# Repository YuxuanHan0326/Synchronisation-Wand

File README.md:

# Synchronisation-Wand
- [Introduction](https://github.com/YuxuanHan0326/Synchronisation-Wand?tab=readme-ov-file#introduction)
- [Related Publications](https://github.com/YuxuanHan0326/Synchronisation-Wand?tab=readme-ov-file#related-publications)
- [Project Files and Documentation](https://github.com/YuxuanHan0326/Synchronisation-Wand?tab=readme-ov-file#project-files-and-documentation)
- [3D Design Overview](https://github.com/YuxuanHan0326/Synchronisation-Wand?tab=readme-ov-file#3d-design-overview)
- [Screen Overview](https://github.com/YuxuanHan0326/Synchronisation-Wand?tab=readme-ov-file#screen-overview)
- [PCB Design](https://github.com/YuxuanHan0326/Synchronisation-Wand?tab=readme-ov-file#pcb-design)
- [Basic Controls](https://github.com/YuxuanHan0326/Synchronisation-Wand?tab=readme-ov-file#basic-controls)
- [Flash the Firmware](https://github.com/YuxuanHan0326/Synchronisation-Wand?tab=readme-ov-file#flash-the-firmware)
- [Configure Parameters of the Firmware](https://github.com/YuxuanHan0326/Synchronisation-Wand?tab=readme-ov-file#configure-parameters-of-the-firmware)

## Project Files and Documentation
This repository contains the Synchronisation Wand hardware and firmware, plus the verification platform for the encoded EMP synchronisation method. For fast access:
- [Synchronisation Wand Firmware](https://github.com/YuxuanHan0326/Synchronisation-Wand/tree/main/Firmware)
- [Synchronisation Wand PCB](https://github.com/YuxuanHan0326/Synchronisation-Wand/tree/main/PCB%20V1)
- [Data Processing Script for Verification Platform](https://github.com/YuxuanHan0326/Synchronisation-Wand/tree/main/Verification/DataProcessing/scripts)
- [Collected Source Data](https://github.com/YuxuanHan0326/Synchronisation-Wand/tree/main/Verification/DataProcessing/data)
- [Verilog Implementation Files for Testbed](https://github.com/YuxuanHan0326/Synchronisation-Wand/tree/main/Verification/Testbed/new_single_synchronisation.srcs/sources_1/new)
- [Final Report](./Resources/docs/Final_Report.pdf)
- [Presentation Poster](./Resources/docs/Presentation_Poster.pdf)

The related publication focuses mainly on the Synchronisation Wand device and hardware design. The final report is complementary and covers the verification platform, encoded EMP synchronisation verification, data processing workflow, and analysis in more detail. The presentation poster is a concise visual summary of the verification work.

## Introduction
The *Synchronisation Wand* is an open-source hardware solution for synchronising multiple wireless inertial measurement unit sensors (IMU) using their onboard magnetometers. The device combines an ESP32-S3 micro-controller unit with an electromagnetic generator to create an encoded electromagnetic event which can be used to synchronise multiple IMU devices. The device also includes an onboard IMU, allowing the user to track the motion of the wand as well as perform a kinetic synchronising event.

The device includes an OLED display and 4 configuable push buttons for user interface to enhance the usability of the system. The device uses SD card as storage medium to store the synchronising data and onboard IMU data. WiFi is used to synchronise the RTC using SNTP from configurable NTP servers, e.g. *pool.ntp.org*.

## Related Publications
For further detail of this project:

- [The Wand Chooses the IMU - Open Source Hardware for Synchronising Wearables using Magnetometer](https://dl.acm.org/doi/10.1145/3675094.3678485)

For how the electromagnetic synchronising method works:

- [A magnetometer-based method for in-situ syncing of wearable inertial measurement units](https://doi.org/10.3389/fcomp.2024.1385392)

## 3D Design Overview

## Screen Overview

## PCB Design
The PCB of the synchronisation wand is designed using the open sourced PCB design software *KiCad*. The PCB files are completely open-sourced.

### Schematic

### Layout

### Stack-up Information
This device uses a 4 layer pcb, with a stack up of Signal-GND-GND-Signal.
The physical stack up of the pcb board is shown below:

## Basic Controls
- Press "MENU" button to switch between menus.
- Press "S-MENU" button to switch submenus.
- Press "ACT" button to activate / deactive functions.
- Long press for more than 4 seconds and release to put the device into deep sleep mode. Re-click the button to wake the device up.

**Note:**
Before performing IMU synchronisation or turning on onboard IMU, please make sure that WiFi is connected, time has been synchronised and SD card is plugged in and recognised.

To avoid data loss, the user should terminate the synchronisation group, turn off onboard IMU manually and use the *Eject* function under the *SD Card* menu before unplugging the SD card.

## Flash the Firmware
### Requirements
To change and rebuild the firmware, the Espressif's IoT Development Framework (ESP-IDF) is needed. Installation instructions for the latest version of the ESP-IDF can be found in [this documentation](https://docs.espressif.com/projects/esp-idf/en/latest/esp32/get-started/). The firmware is tested on ESP-IDF version 5.2.1.

### ESP32S3 External Oscillator issue in ESP-IDF 5.2.1
ESP-IDF 5.2.1 has an ESP32-S3 RTC 32 kHz external oscillator setup issue: the clock tree code applies the internal 32 kHz crystal driver settings to the external oscillator path. On this hardware, the default values do not reliably drive the RTC slow clock.

If you build with ESP-IDF 5.2.1, manually override the XTAL32K configuration in the ESP-IDF clock tree source with these recommended starting values:

```c
.dac  = 0,
.dres = 0,
.dgm  = 0,
.dbuf = 1,
```

Alternatively, try a newer ESP-IDF release, where the ESP32-S3 external oscillator path may already be fixed. To confirm whether the oscillator started correctly, check the warning log printed during device power-up. If the RTC 32 kHz oscillator is not detected, the firmware will report a startup warning and fall back to the internal RTC clock source.

### Build and Flash using UART
By default, the device can be flashed using UART. The user can connect the auxiliary UART pins to the computer through a USB-Serial converter. Ensure that the signal line voltage of the converter is set to 3.3V before connecting to the device.

With ESP-IDF on your `$PATH`, you can use `idf.py` to build the application from within this directory:

```bash
idf.py build
```

To flash the device, the user need to first set the device into bootloader mode:
1. Power up the device
2. Press and hold "BOOT" button
3. Click and release "RESET" button
4. Release "BOOT" button
The device will then be reset in bootloader mode and ready for flashing.

After properly configured the chip type and serial port number, the user can flash the firmware by using:
```bash
idf.py flash
```
When the flash complete message is shown up, click "RESET" to reset the device, and the flashing will complete.

### Monitor the device
By default, the device's log messages can be monitored by using UART. This can be achieved by typing the following command in the ESP-IDF terminal:
```bash
idf.py monitor
```

### Build and flash using DFU (Direct Firmware update) via USB 2.0 Full Speed
The device can also being build and flashed to the device via USB 2.0 full speed, but requires extra settings. Please navigate to [this documentation](https://docs.espressif.com/projects/esp-idf/en/latest/esp32s3/api-guides/dfu.html) for details.

## Configure Parameters of the Firmware
The compile-time defaults are defined in [`Firmware/main/user_config.h`](./Firmware/main/user_config.h). These values are used as the firmware's initial configuration after a build/flash, but they are no longer the only way to configure the device.

At runtime, the firmware exposes a BLE GATT interface. After powering the device, connect with a BLE client to the device named `SYNCHRONISATION WAND`, then read or write the relevant characteristics:

| BLE service | Runtime parameters |
| --- | --- |
| WiFi Service | WiFi SSID and WiFi password. |
| Synchronisation Parameters Service | Point of interest, maximum sync error, target IMU sample period, and sync signal pulse width. |
| Synchronisation Parameters Service | Sync signal duration is read/notify only. It is calculated by the firmware from the synchronisation settings. |
| On-board IMU Settings Service | On-board IMU status is read only; on-board IMU sample period is writable. |

WiFi values and floating-point synchronisation parameters are transferred as strings. Integer parameters use the raw GATT value type implemented in the firmware. The current BLE service UUIDs, characteristic UUIDs, access permissions, and value handling are defined in [`Firmware/main/ble_gatt.h`](./Firmware/main/ble_gatt.h) and [`Firmware/main/ble_gatt.c`](./Firmware/main/ble_gatt.c).

For more background on the verification platform, encoded EMP synchronisation verification, data processing workflow, and analysis, see the [Final Report](./Resources/docs/Final_Report.pdf).

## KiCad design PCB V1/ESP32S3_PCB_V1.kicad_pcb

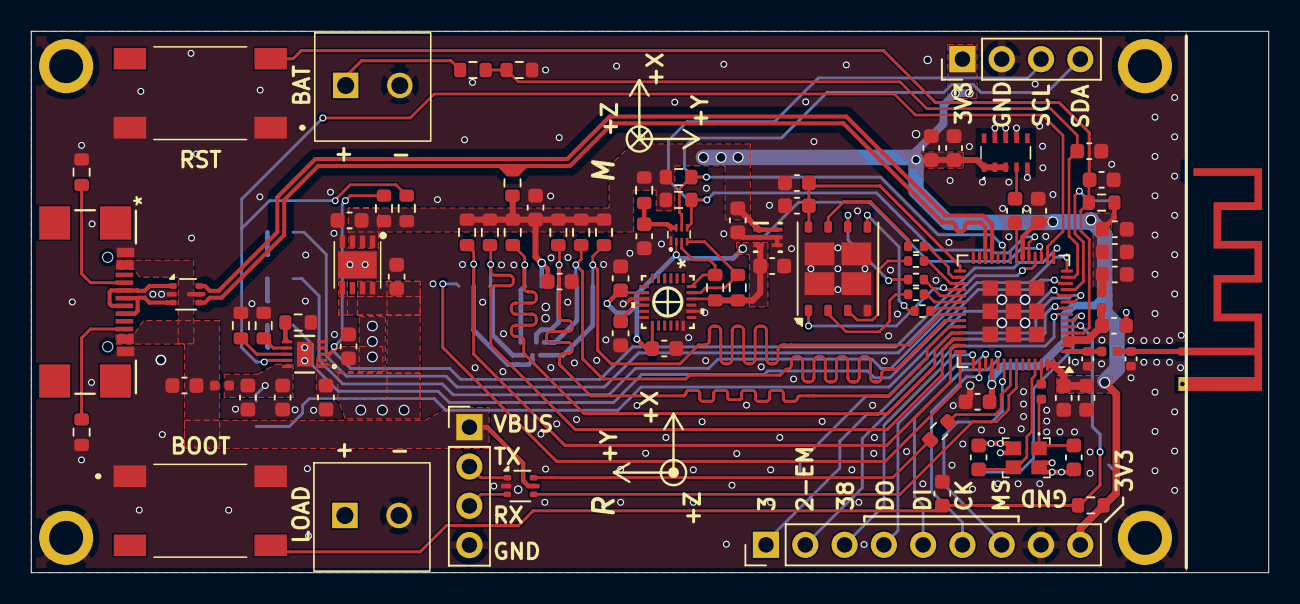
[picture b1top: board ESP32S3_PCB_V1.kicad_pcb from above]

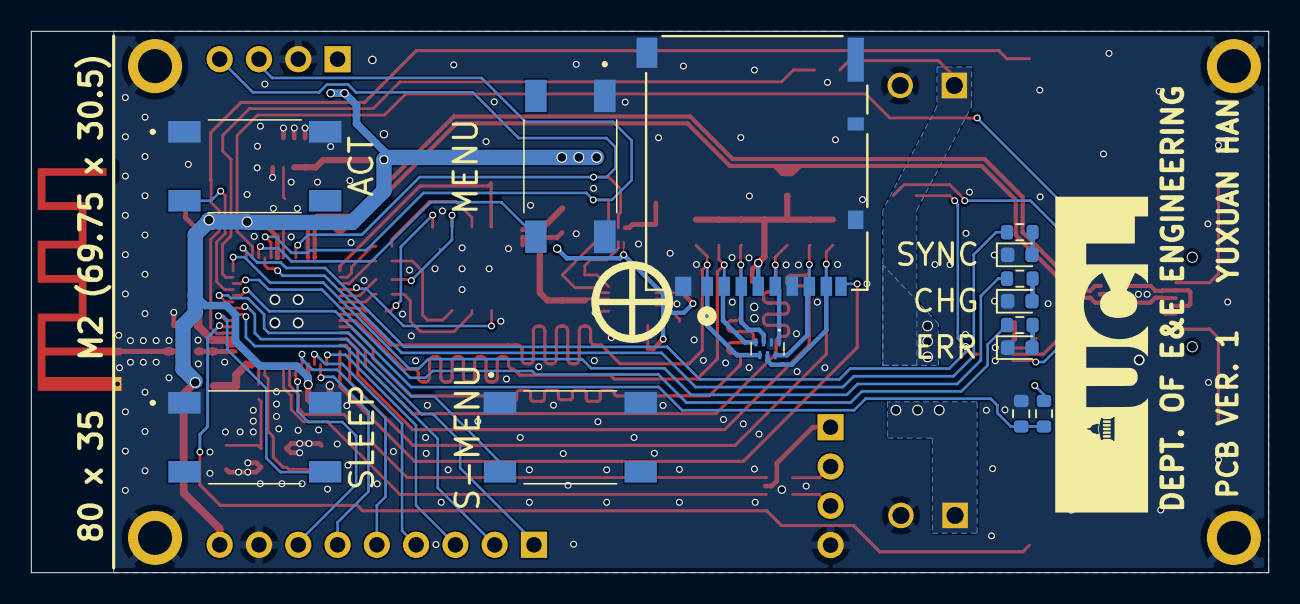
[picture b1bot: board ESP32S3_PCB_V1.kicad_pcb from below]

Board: 4 copper layers, 80.0 x 35.0 mm, 106 parts (14 on the bottom side), 77 nets.

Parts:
ACT: SW_Push; Switch
AE1: Antenna 2.4GHz; Texas_SWRA117D_2.4GHz_Left
BAT: Conn_01x02_Socket; CTB30512BK
BOOT: SW_Push; Switch
C1, C2, C7, C11, C12, C13, C16, C17, C18, C23, C24, C28, C31, C33, C34: 0.1uF; C_0603_1608Metric
C3, C5, C6, C9, C14, C20, C25, C29, C32: 1uF; C_0603_1608Metric
C4, C8, C10, C26, C35: 10uF; C_0603_1608Metric
C15: 18pF; C_0603_1608Metric
C19: 0.01uF; C_0603_1608Metric
C21, C22: 1.8pF; C_0402_1005Metric
C27, C30: 10pF; C_0603_1608Metric
CHG: LED; LED_0603_1608Metric
ERR: LED; LED_0603_1608Metric
H1, H2, H3, H4: MountingHole_Pad; MountingHole_2.2mm_M2_ISO7380_Pad
J1: USB4110-GF-A; USB4110-GF-A_GCT
J2, J6: Conn_01x04_Pin; PinHeader_1x04_P2.54mm_Vertical
J4: Conn_01x09_Pin; PinHeader_1x09_P2.54mm_Vertical
J5: DM3AT-SF-PEJM540; CONN8_DM3AT-SF-PEJM5_HIR
L1: 2.2nH; L_0402_1005Metric
L2: 24nH; L_0402_1005Metric
L3: 2.7nH; L_0402_1005Metric
L4: 2nH; L_0402_1005Metric
LOAD: Conn_01x02_Socket; CTB30512BK
MENU: SW_Push; Switch
R1, R2, R34: 5K1; R_0603_1608Metric
R3, R4, R7, R24, R25, R26, R27, R28, R29, R35: 10K; R_0603_1608Metric
R5, R6: 100K; R_0603_1608Metric
R8: 560; R_0603_1608Metric
R9: 18K; R_0603_1608Metric
R10: 33K; R_0603_1608Metric
R11: 82K; R_0603_1608Metric
R12: 1K5; R_0603_1608Metric
R15, R16, R31, R33: 3K3; R_0603_1608Metric
R17, R18, R19, R20, R21: 0; R_0402_1005Metric
R22: 499; R_0603_1608Metric
R23: 200K; R_0603_1608Metric
R30, R32: 1K; R_0603_1608Metric
R36: 470; R_0603_1608Metric
RST: SW_Push; Switch
S-MENU: SW_Push; Switch
SLEEP: SW_Push; Switch
SYNC: LED; LED_0603_1608Metric
U1, U2: USBLC6-2P6; SOT-666
U3: BQ25185DLHR; WSON10_DLH_TEX
U4: NCV59801CML330TCG; SON65P300X300X100-9N-D
U5: TLV70018DSER; DSE0006A
U6: ICM-20948; QFN24_3X3X0P9_IVS
U7: ESP32-S3; QFN-56-1EP_7x7mm_P0.4mm_EP4x4mm
U8: PCA9306DQER
U9: PUSB3FR6Z
U10: GD25Q256EWIGR; WSON-8-1EP_6x5mm_P1.27mm_EP3.4x4.3mm
Y1: 830108208709
Y2: TG-3541CE_32.7680KXA3; TG3541CE327680KXA3

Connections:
+1V8: C9.1, C13.2, C17.1, R15.1, R16.1, U5.3 (OUT), U6.8 (VDDIO), U6.13 (VDD), U6.22 (nCS), U8.2 (VREF1)
+3.3V: C5.1, C10.1, C16.1, C18.1, C19.1, C20.1, C24.1, C25.1, C26.1, C28.2, C29.2, C34.1, C35.1, J4.9, J5.4 (VDD), J6.1, L4.2, R3.1, R4.1, R12.1, R23.1, R24.1, R25.1, R26.1, R27.1, R28.1, R29.1, R31.2, R33.2, R34.1, R35.1, U4.1 (OUT_1), U4.2 (OUT_2), U4.3 (FB/SNS), U5.1 (IN), U5.6 (EN), U7.20 (VDD3P3_RTC), U7.46 (VDD3P3_CPU), U7.55 (VDDA), U7.56 (VDDA), Y2.1 (OE), Y2.2 (VCC), Y2.3 (VCC)
/<NO NET>: R17.2, U10.7 (HOLD#/RESET#(IO3))
/ACTIVATE: ACT.2, U7.11 (GPIO6)
/CHIP_PU: C32.1, R35.2, RST.2, U7.4 (CHIP_PU)
/CLK_32K: C15.1, Y2.4 (OUT)
/D+: J1.A6 (DP1), J1.B6 (DP2), U2.3 (I/O2)
/D-: J1.A7 (DN1), J1.B7 (DN2), U2.1 (I/O1)
/DEEP_SLEEP: SLEEP.2, U7.6 (GPIO1)
/ELECTROMAGNET: J4.2, U7.7 (GPIO2)
/GPIO0: BOOT.2, C31.1, R34.2, U7.5 (GPIO0)
/GPIO3: J4.1, U7.8 (GPIO3)
/GPIO38: J4.3, U7.43 (GPIO38)
/LED1: R30.1, U7.12 (GPIO7)
/LED2: R32.1, U7.14 (GPIO9)
/LED3: R36.1, U7.18 (GPIO13)
/MENU: MENU.2, U7.17 (GPIO12)
/MTCK: J4.6, U7.44 (MTCK)
/MTDI: J4.5, U7.47 (MTDI)
/MTDO: J4.4, U7.45 (MTDO)
/MTMS: J4.7, U7.48 (MTMS)
/SCL: J6.3, R31.1, U7.19 (GPIO14), U8.5 (SCL2)
/SDA: J6.4, R33.1, U7.23 (GPIO17), U8.6 (SDA2)
/SD_CARD_DETECT: J5.9 (Card_Detect), U7.42 (GPIO37)
/SD_CLK: J5.5 (CLK), R24.2, U7.39 (GPIO34), U9.1 (CH1)
/SD_CMD: J5.3 (CMD), R25.2, U7.38 (GPIO33), U9.3 (CH2)
/SD_DAT0: J5.7 (DAT0), R29.2, U7.40 (GPIO35), U9.7 (CH6)
/SD_DAT1: J5.8 (DAT1), R28.2, U7.41 (GPIO36), U9.6 (CH5)
/SD_DAT2: J5.1 (DAT2), R27.2, U7.36 (SPICLK_N), U9.5 (CH4)
/SD_DAT3: J5.2 (CD/DAT3), R26.2, U7.37 (SPICLK_P), U9.4 (CH3)
/SPICLK: R19.2, U10.6 (SCLK)
/SPICS0: U7.32 (SPICS0), U10.1 (CS#)
/SPID: R21.2, U10.5 (SI(IO0))
/SPIQ: R20.2, U10.2 (SO(IO1))
/SPIWP: R18.2, U10.3 (WP#(IO2))
/STAT1: R3.2, U3.9 (STAT1), U7.16 (GPIO11)
/STAT2: R4.2, U3.3 (STAT2), U7.15 (GPIO10)
/SUBMENU: S-MENU.2, U7.9 (GPIO4)
/SYS: C4.1, C8.1, LOAD.1, U3.1 (SYS), U4.5 (EN), U4.7 (IN_1), U4.8 (IN_2)
/U0RXD: U1.4 (I/O2), U7.50 (U0RXD)
/U0TXD: R22.2, U1.6 (I/O1)
/USB_D+: R12.2, U2.4 (I/O2), U7.26 (GPIO20/USB_D+)
/USB_D-: U2.6 (I/O1), U7.25 (GPIO19/USB_D-)
/VBAT_SENSE: C7.1, R10.2, R11.1, U7.13 (GPIO8)
/VBUS_FILT: C2.1, C3.1, L1.2, R5.1, U3.10 (IN)
/VBUS_MONITOR: R5.2, R6.1, U7.10 (GPIO5)
/VDD3P3: C23.1, L4.1, U7.2 (VDD3P3), U7.3 (VDD3P3)
/VDD_SPI: C11.1, C14.1, U7.29 (VDD_SPI), U10.8 (VCC)
/XIN: C27.1, L2.1, Y1.1 (CRYSTAL_1)
/XOUT: C30.1, U7.53 (XTAL_N), Y1.3 (CRYSTAL_2)
GND: ACT.1, AE1.2 (Ground_Via), BAT.2, BOOT.1, C1.2, C2.2, C3.2, C4.2, C5.2, C6.2, C7.2, C8.2, C9.2, C10.2, C11.2, C12.2, C13.1, C14.2, C16.2, C17.2, C18.2, C19.2, C20.2, C21.2, C22.2, C23.2, C24.2, C25.2, C26.2, C27.2, C28.1, C29.1, C30.2, C31.2, C32.2, C33.2, C34.2, C35.2, CHG.1 (K), ERR.1 (K), H1.1, H2.1, H3.1, H4.1, J1.A1-B12 (GND), J1.A12-B1 (GND), J2.4, J4.8, J5.6 (VSS), J5.10 (MP1), J5.11 (MP2), J5.12 (MP3), J5.13 (MP4), J5.14 (MP5), J6.2, LOAD.2, MENU.1, R1.2, R2.2, R6.2, R7.1, R8.2, R9.2, R11.2, RST.1, S-MENU.1, SLEEP.1, SYNC.1 (K), U1.2 (GND), U2.2 (GND), U3.4 (/CE), U3.5 (GND), U3.11 (EPAD), U4.4 (GND), U4.9 (EP), U5.2 (GND), U5.4 (NC), U5.5 (NC), U6.9 (SDO/AD0), U6.18 (GND), U6.20 (RESV_GND), U7.57 (GND), U8.1 (GND), U9.2 (GND), U10.4 (VSS), U10.9 (VSS), Y1.2 (GND_1), Y1.4 (GND_2), Y2.5 (GND), Y2.7 (GND), Y2.8 (GND), Y2.9 (GND)
unnamed: AE1.1 (Feed_Point), C22.1, L3.2
unnamed: ERR.2 (A), R30.2
unnamed: CHG.2 (A), R32.2
unnamed: R36.2, SYNC.2 (A)
unnamed: J1.A5 (CC1), R2.1
unnamed: J1.B5 (CC2), R1.1
unnamed: J2.2, U1.1 (I/O1)
unnamed: J2.3, U1.3 (I/O2)
unnamed: R9.1, U3.7 (ILIM/VSET)
unnamed: R8.1, U3.8 (ISET)
unnamed: R7.2, U3.6 (TS/MR)
unnamed: C12.1, U6.10 (REGOUT)
unnamed: R15.2, U6.23 (SCL/SCLK), U8.4 (SCL1)
unnamed: R16.2, U6.24 (SDA/SDI), U8.3 (SDA1)
unnamed: C21.1, L3.1, U7.1 (LNA_IN)
unnamed: R19.1, U7.33 (SPICLK)
unnamed: R21.1, U7.35 (SPID)
unnamed: R17.1, U7.30 (SPIHD)
unnamed: R20.1, U7.34 (SPIQ)
unnamed: R18.1, U7.31 (SPIWP)
unnamed: R22.1, U7.49 (U0TXD)
unnamed: C15.2, U7.21 (XTAL_32K_P)
unnamed: L2.2, U7.54 (XTAL_P)
unnamed: C33.1, R23.2, U8.7 (VREF2), U8.8 (EN)
VBAT: BAT.1, C6.1, R10.1, U3.2 (BAT)
VBUS: C1.1, J1.A4-B9 (VBUS), J1.A9-B4 (VBUS), J2.1, L1.1, U1.5 (VBUS), U2.5 (VBUS)

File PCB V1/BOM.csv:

"Reference","Value","Datasheet","Footprint","Qty","DNP"
"C1,C2,C7,C11,C12,C13,C16,C17,C18,C23,C24,C28,C31,C33,C34","0.1uF","~","Capacitor_SMD:C_0603_1608Metric","15",""
"C3,C5,C6,C9,C14,C20,C25,C29,C32","1uF","~","Capacitor_SMD:C_0603_1608Metric","9",""
"C4,C8,C10,C26,C35","10uF","~","Capacitor_SMD:C_0603_1608Metric","5",""
"C15","18pF","~","Capacitor_SMD:C_0603_1608Metric","1",""
"C19","0.01uF","~","Capacitor_SMD:C_0603_1608Metric","1",""
"C21,C22","1.8pF","~","Capacitor_SMD:C_0402_1005Metric","2",""
"C27,C30","10pF","~","Capacitor_SMD:C_0603_1608Metric","2",""
"D1,D2,D3","LED","~","LED_SMD:LED_0603_1608Metric","3",""
"J1","USB4110-GF-A","USB4110-GF-A","Project_Component_Footprints:USB4110-GF-A_GCT","1",""
"J2,J6","Conn_01x04_Pin","~","Connector_PinHeader_2.54mm:PinHeader_1x04_P2.54mm_Vertical","2",""
"J3,J7","Conn_01x02_Socket","~","Project_Component_Footprints:CTB30512BK","2",""
"J4","Conn_01x09_Pin","~","Connector_PinHeader_2.54mm:PinHeader_1x09_P2.54mm_Vertical","1",""
"J5","DM3AT-SF-PEJM540","DM3AT-SF-PEJM540","Project_Component_Footprints:CONN8_DM3AT-SF-PEJM5_HIR","1",""
"L1","2.2nH","~","Inductor_SMD:L_0402_1005Metric","1",""
"L2","24nH","~","Inductor_SMD:L_0402_1005Metric","1",""
"L3","2.7nH","~","Inductor_SMD:L_0402_1005Metric","1",""
"L4","2nH","~","Inductor_SMD:L_0402_1005Metric","1",""
"R1,R2,R34","5K1","~","Resistor_SMD:R_0603_1608Metric","3",""
"R3,R4,R7,R24,R25,R26,R27,R28,R29,R35","10K","~","Resistor_SMD:R_0603_1608Metric","10",""
"R5,R6","100K","~","Resistor_SMD:R_0603_1608Metric","2",""
"R8","560","~","Resistor_SMD:R_0603_1608Metric","1",""
"R9","18K","~","Resistor_SMD:R_0603_1608Metric","1",""
"R10","33K","~","Resistor_SMD:R_0603_1608Metric","1",""
"R11","82K","~","Resistor_SMD:R_0603_1608Metric","1",""
"R12","1K5","~","Resistor_SMD:R_0603_1608Metric","1",""
"R15,R16,R31,R33","3K3","~","Resistor_SMD:R_0603_1608Metric","4",""
"R17,R18,R19,R20,R21","0","~","Resistor_SMD:R_0402_1005Metric","5",""
"R22","499","~","Resistor_SMD:R_0603_1608Metric","1",""
"R23","200K","~","Resistor_SMD:R_0603_1608Metric","1",""
"R30,R32","1K","~","Resistor_SMD:R_0603_1608Metric","2",""
"R36","470","~","Resistor_SMD:R_0603_1608Metric","1",""
"SW1,SW2,SW3,SW4,SW5,SW6","SW_Push","~","Project_Component_Footprints:Switch","6",""
"U1,U2","USBLC6-2P6","https://www.st.com/resource/en/datasheet/usblc6-2.pdf","Package_TO_SOT_SMD:SOT-666","2",""
"U3","BQ25185DLHR","BQ25185DLHR","Project_Component_Footprints:WSON10_DLH_TEX","1",""
"U4","NCV59801CML330TCG","https://www.onsemi.com/download/data-sheet/pdf/ncv59801-d.pdf","Project_Component_Footprints:SON65P300X300X100-9N-D","1",""
"U5","TLV70018DSER","TLV70018DSER","Project_Component_Footprints:DSE0006A","1",""
"U6","ICM-20948","ICM-20948","Project_Component_Footprints:QFN24_3X3X0P9_IVS","1",""
"U7","ESP32-S3","https://www.espressif.com/sites/default/files/documentation/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","Package_DFN_QFN:QFN-56-1EP_7x7mm_P0.4mm_EP4x4mm","1",""
"U8","PCA9306DQER","http://www.ti.com/lit/ds/symlink/pca9306.pdf","Project_Component_Footprints:PCA9306DQER","1",""
"U9","PUSB3FR6Z","https://assets.nexperia.com/documents/data-sheet/PUSB3FR6.pdf","Project_Component_Footprints:PUSB3FR6Z","1",""
"U10","GD25Q256EWIGR","https://s3.amazonaws.com/snapeda/datasheet/GD25Q256EWIGR_Gig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","Package_SON:WSON-8-1EP_6x5mm_P1.27mm_EP3.4x4.3mm","1",""
"Y1","830108208709","https://www.we-online.com/components/products/datasheet/8301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","Project_Component_Footprints:830108208709","1",""
"Y2","TG-3541CE_32.7680KXA3","https://datasheet.datasheetarchive.com/originals/distributor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","Project_Component_Footprints:TG3541CE327680KXA3","1",""

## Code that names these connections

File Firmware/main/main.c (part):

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        .pin_bit_mask = (1ULL << PIN_TS_DEEP_SLEEP) | (1ULL << PIN_TS_MENU) | (1ULL << PIN_TS_SUBMENU) | (1ULL << PIN_TS_ACTIVATE)};
    ESP_ERROR_CHECK(gpio_config(&GPIO_config_TS));

    // Configure LED GPIOs and Electromagnet GPIO
    gpio_config_t GPIO_config_LED = {
        .intr_type = GPIO_INTR_DISABLE,
        .mode = GPIO_MODE_OUTPUT,
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    prev_cd_gpio_status = gpio_get_level(PIN_SD_DETECT);
    if (prev_cd_gpio_status == 0)
    {
        if (sd_card_init(PIN_SD_CLK, PIN_SD_CMD, PIN_SD_DAT0, PIN_SD_DAT1, PIN_SD_DAT2, PIN_SD_DAT3) == ESP_OK)
        {
            system_status.sd_connected = 1;
            strcpy(sd_sub_1.value, "Connected");
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// Detect Charge Status
static void detect_charge_status(void)
{
    int stat1 = gpio_get_level(PIN_CHG_STAT1);
    int stat2 = gpio_get_level(PIN_CHG_STAT2);
    const char *TAG = "Charging IC";

    // Case 1: Charge Completed
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            if (system_status.sd_connected == 0)
            {
                vTaskDelay(pdMS_TO_TICKS(100));  // Compensate the time interval between card detected signal and the pins getting properly contacted
                if (sd_card_init(PIN_SD_CLK, PIN_SD_CMD, PIN_SD_DAT0, PIN_SD_DAT1, PIN_SD_DAT2, PIN_SD_DAT3) == ESP_OK)
                {
                    system_status.sd_connected = 1;
                    strcpy(sd_sub_1.value, "Connected");
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
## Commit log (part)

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2024-07-08 Update LICENSE
2024-07-12 Uploaded PCB V1
2024-07-12 Uploaded Firmware
2025-03-31 Updated V2
    Updated V2 of the firmware. Fixed bugs and added BLE support for real time parameter configuation.
2025-04-10 Uploaded verification.
    Uploaded files for the verification of encoded EMP synchronisation method.
2026-06-08 Clean up vivado testbed source control layout following AMD UG892
2026-06-08 Refactored verification data processing part.
2026-06-08 Added FYP documents and updated README
2026-06-08 Update README to inform the ESP-IDF 5.2.1 external oscillator issue
